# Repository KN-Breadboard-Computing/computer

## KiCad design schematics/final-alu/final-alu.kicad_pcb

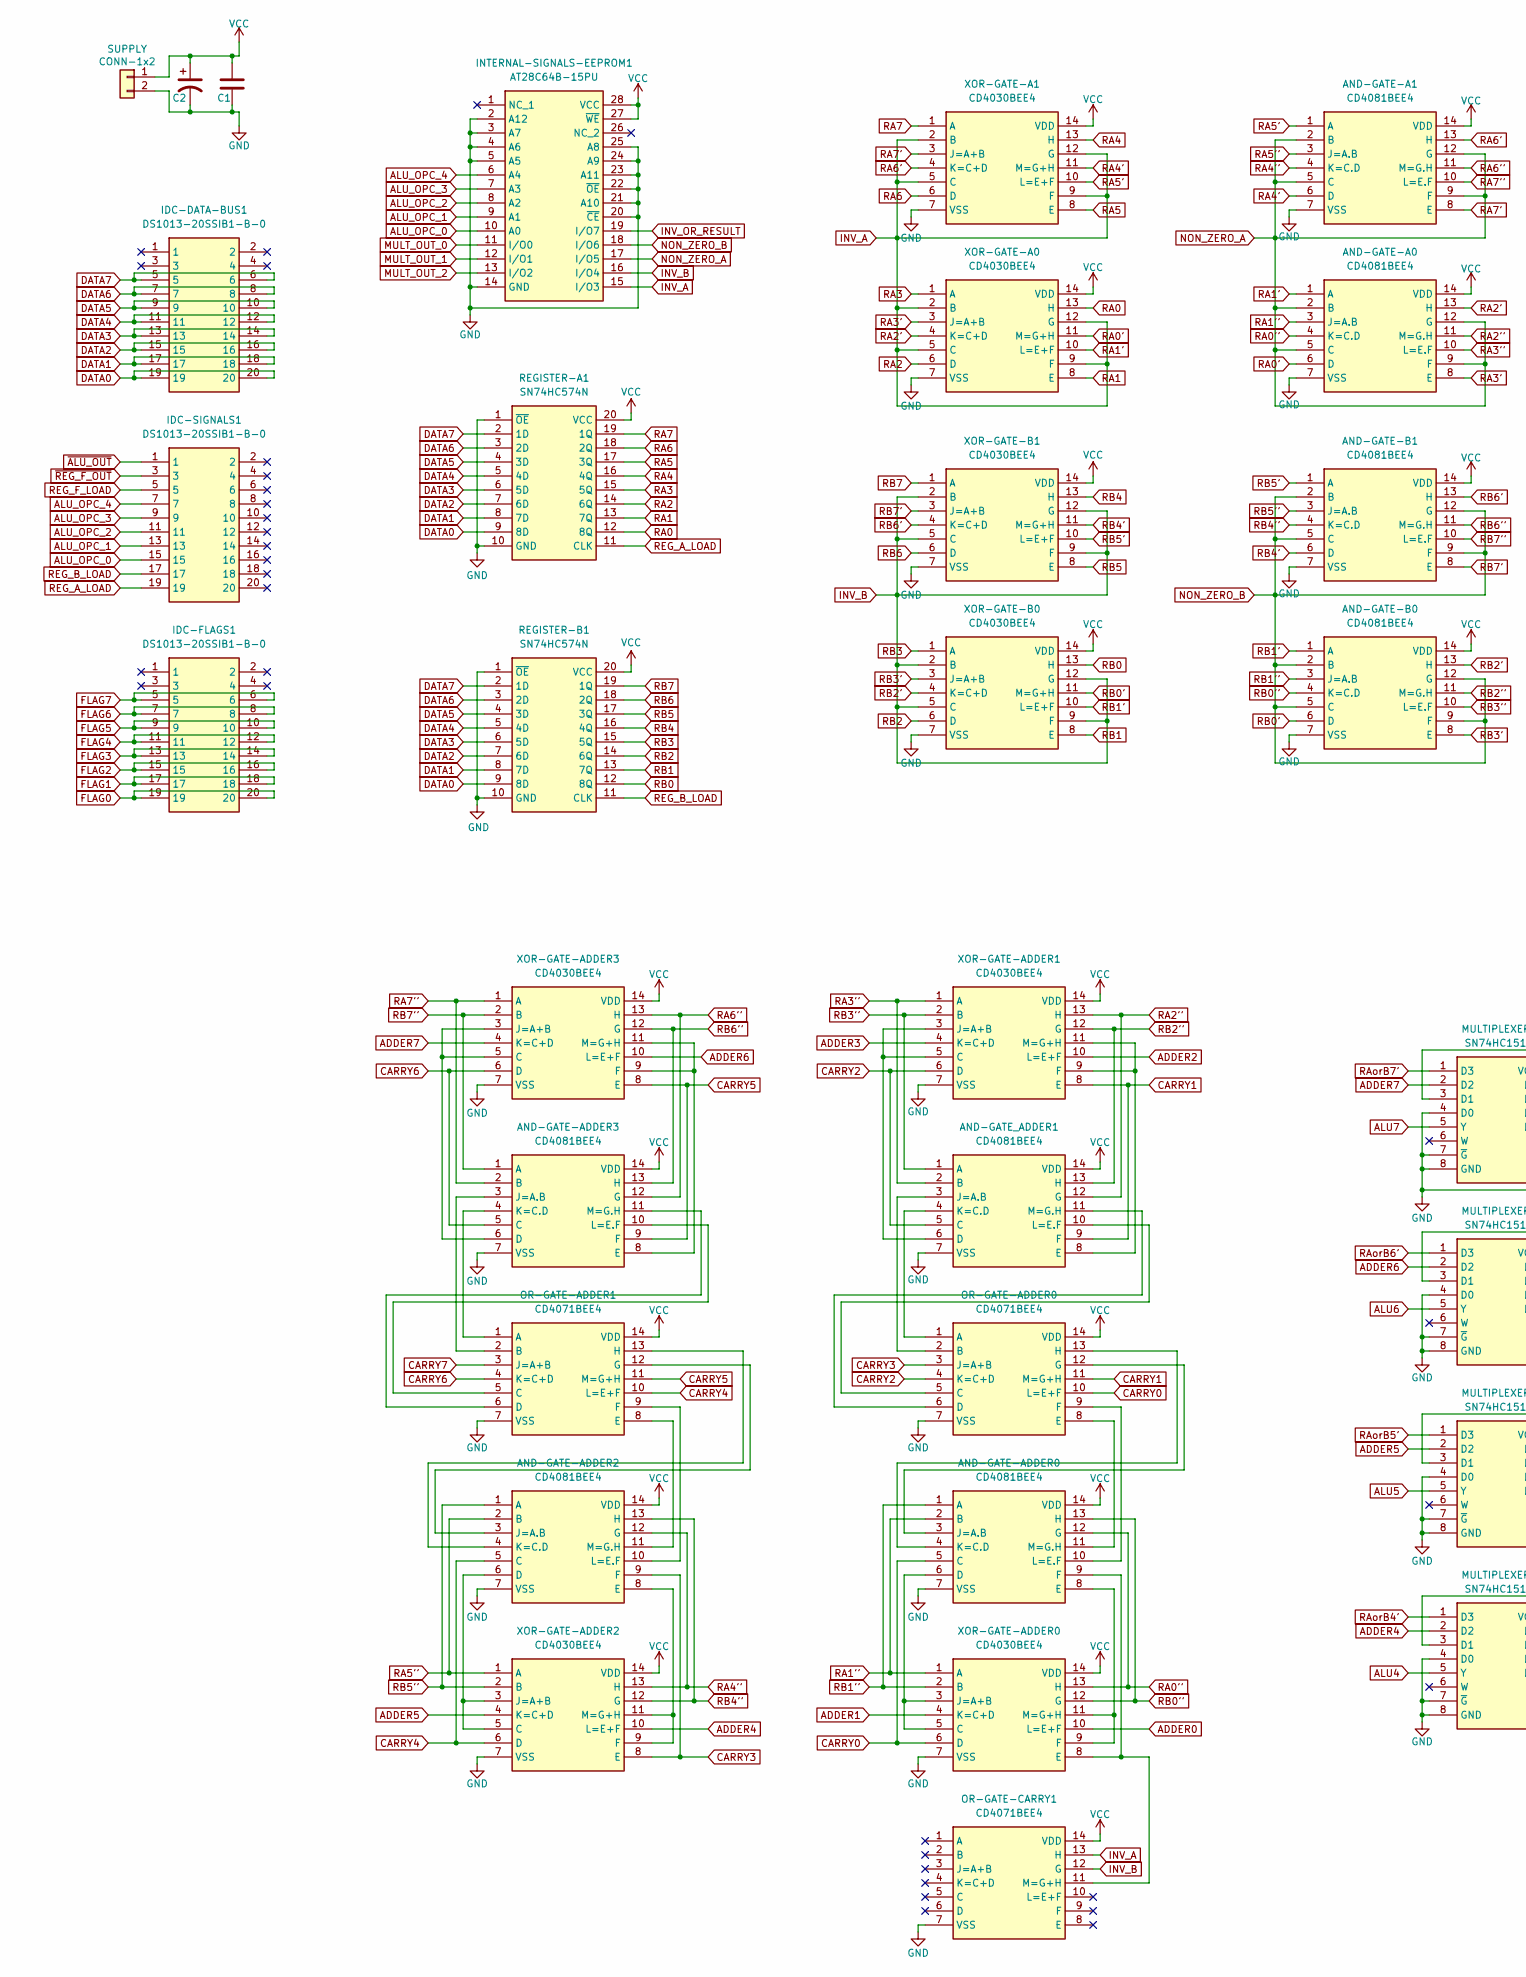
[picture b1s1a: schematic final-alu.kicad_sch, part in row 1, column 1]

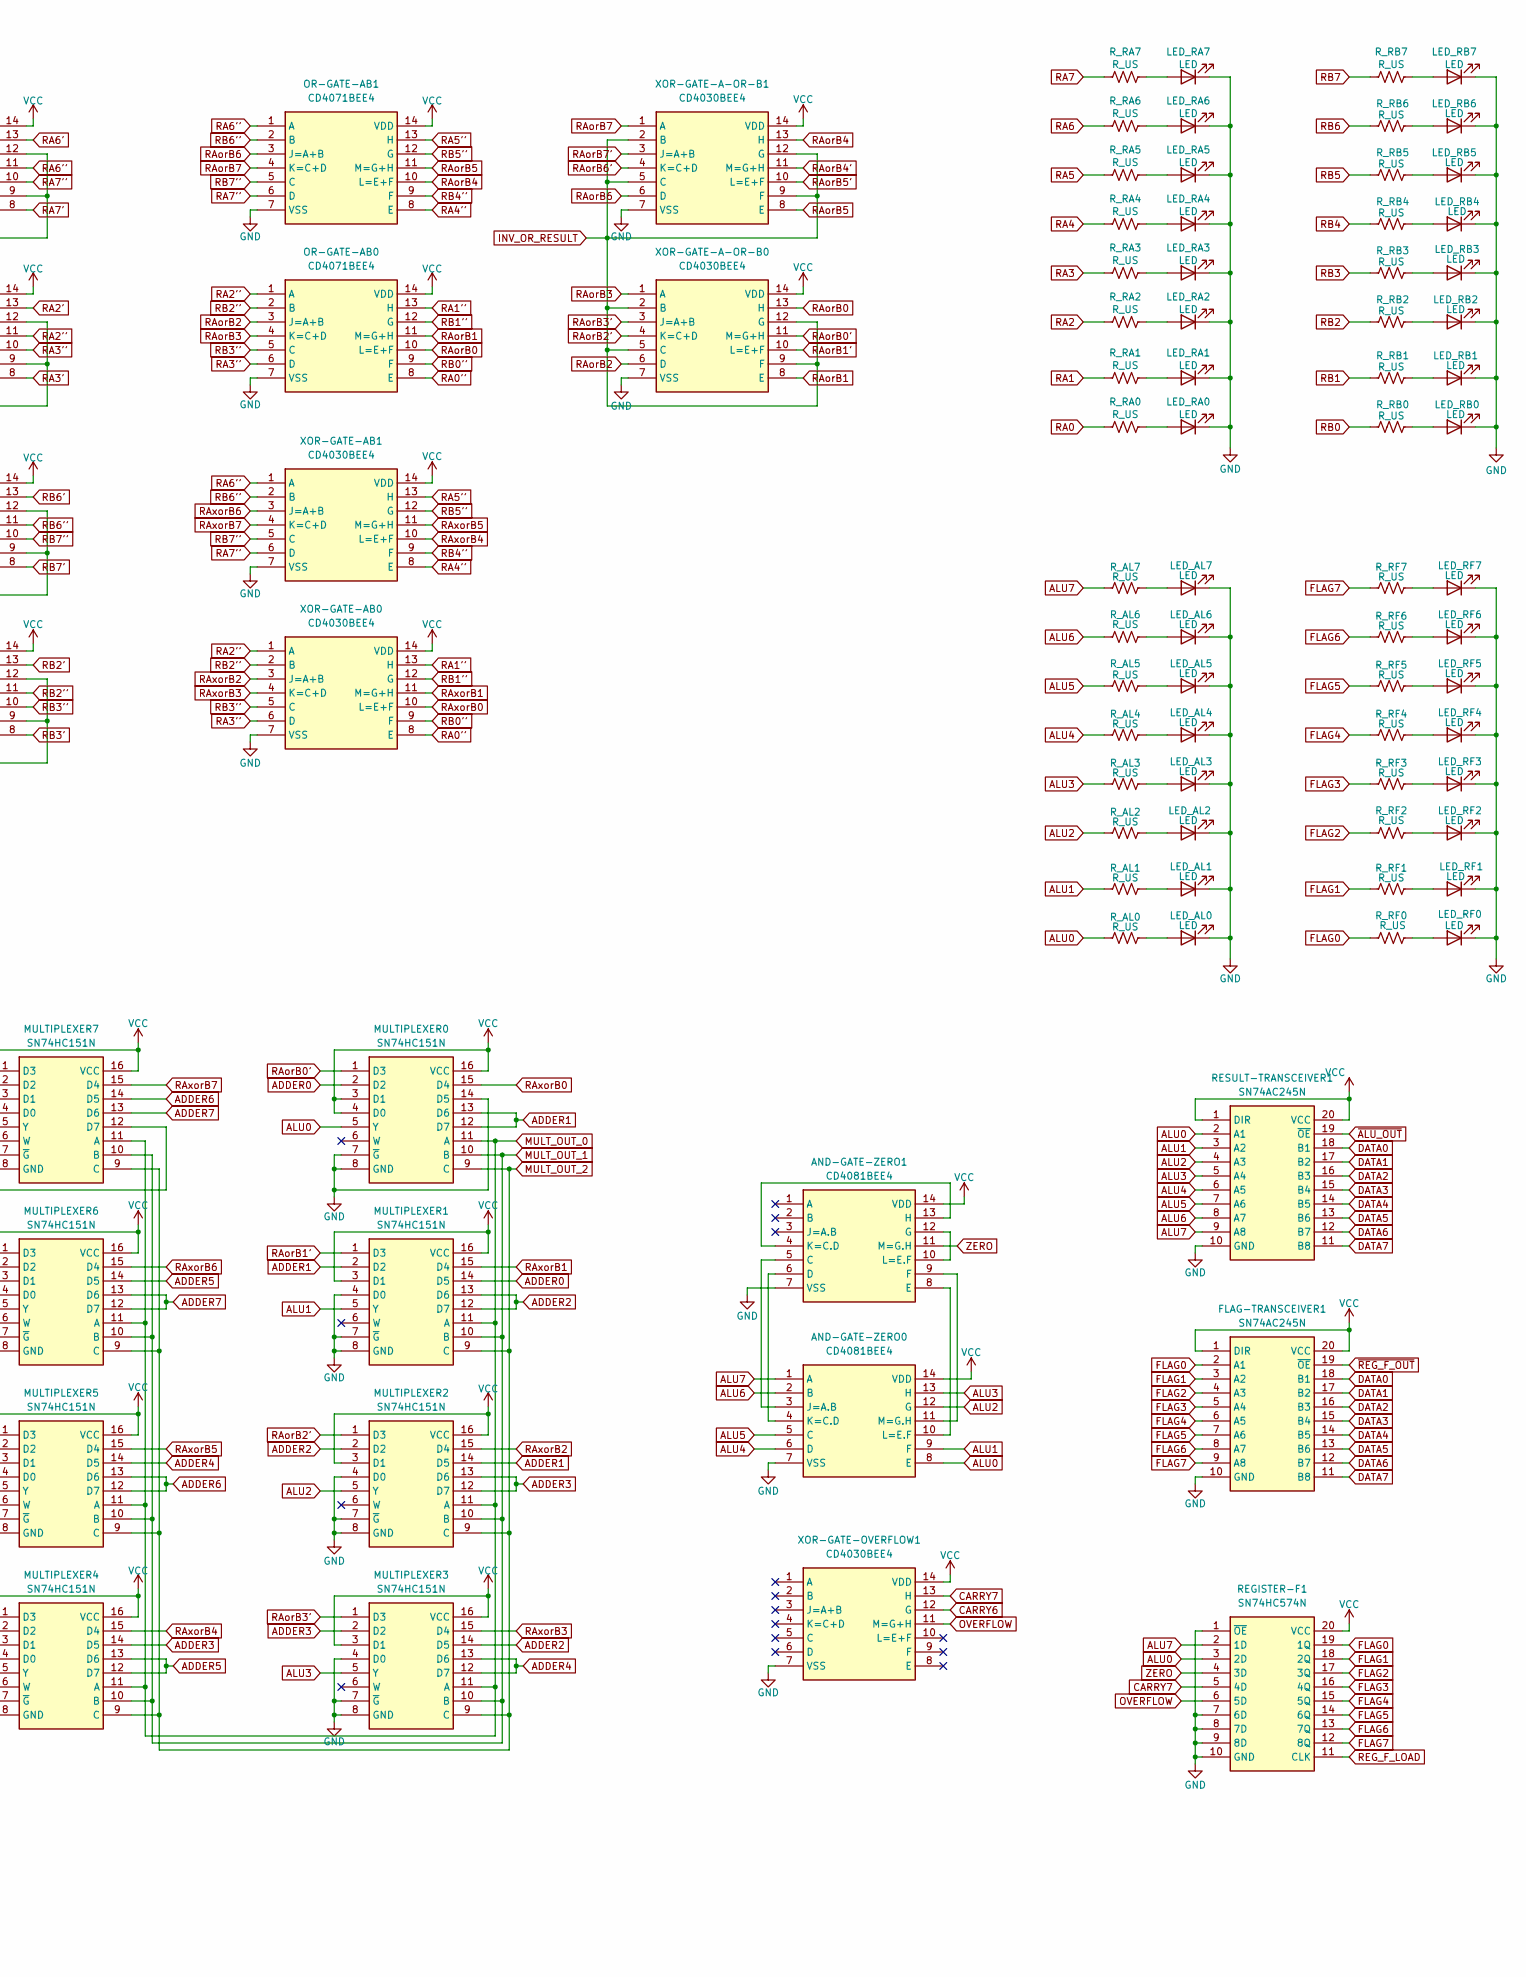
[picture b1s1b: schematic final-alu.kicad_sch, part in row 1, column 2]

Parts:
AND-GATE-A0, AND-GATE-A1: CD4081BEE4; DIP-14_W7.62mm; Mouser Part Number 595-CD4081BEE4
AND-GATE-ADDER0, AND-GATE-ADDER2, AND-GATE-ADDER3: CD4081BEE4; DIP-14_W7.62mm; Mouser Part Number 595-CD4081BEE4
AND-GATE-B0, AND-GATE-B1: CD4081BEE4; DIP-14_W7.62mm; Mouser Part Number 595-CD4081BEE4
AND-GATE-ZERO0, AND-GATE-ZERO1: CD4081BEE4; DIP-14_W7.62mm; Mouser Part Number 595-CD4081BEE4
AND-GATE_ADDER1: CD4081BEE4; DIP-14_W7.62mm; Mouser Part Number 595-CD4081BEE4
C1: C_Disc_D3.0mm_W1.6mm_P2.50mm
C2: CP_Radial_D5.0mm_P2.50mm
FLAG-TRANSCEIVER1: SN74AC245N; DIP-20_W7.62mm; Mouser Part Number 595-SN74AC245N
IDC-DATA-BUS1: DS1013-20SSIB1-B-0; PinSocket_2x10_P2.54mm_Vertical; Manufacturer_Part_Number DS1013-20SSIB1-B-0
IDC-FLAGS1: DS1013-20SSIB1-B-0; PinSocket_2x10_P2.54mm_Vertical; Manufacturer_Part_Number DS1013-20SSIB1-B-0
IDC-SIGNALS1: DS1013-20SSIB1-B-0; PinSocket_2x10_P2.54mm_Vertical; Manufacturer_Part_Number DS1013-20SSIB1-B-0
INTERNAL-SIGNALS-EEPROM1: AT28C64B-15PU; DIP-28_W15.24mm; Mouser Part Number 556-AT28C64B15PU
LED_AL0, LED_AL1, LED_AL2, LED_AL3, LED_AL4, LED_AL5, LED_AL6, LED_AL7: LED; LED_D5.0mm_FlatTop
LED_RA0, LED_RA1, LED_RA2, LED_RA3, LED_RA4, LED_RA5, LED_RA6, LED_RA7: LED; LED_D5.0mm_FlatTop
LED_RB0, LED_RB1, LED_RB2, LED_RB3, LED_RB4, LED_RB5, LED_RB6, LED_RB7: LED; LED_D5.0mm_FlatTop
LED_RF0, LED_RF1, LED_RF2, LED_RF3, LED_RF4, LED_RF5, LED_RF6, LED_RF7: LED; LED_D5.0mm_FlatTop
MULTIPLEXER0, MULTIPLEXER1, MULTIPLEXER2, MULTIPLEXER3, MULTIPLEXER4, MULTIPLEXER5, MULTIPLEXER6, MULTIPLEXER7: SN74HC151N; DIP-16_W7.62mm; Mouser Part Number 595-SN74HC151N
OR-GATE-AB0, OR-GATE-AB1: CD4071BEE4; DIP-14_W7.62mm; Mouser Part Number 595-CD4071BEE4
OR-GATE-ADDER0, OR-GATE-ADDER1: CD4071BEE4; DIP-14_W7.62mm; Mouser Part Number 595-CD4071BEE4
OR-GATE-CARRY1: CD4071BEE4; DIP-14_W7.62mm; Mouser Part Number 595-CD4071BEE4
REGISTER-A1: SN74HC574N; DIP-20_W7.62mm; Mouser Part Number 595-SN74HC574N
REGISTER-B1: SN74HC574N; DIP-20_W7.62mm; Mouser Part Number 595-SN74HC574N
REGISTER-F1: SN74HC574N; DIP-20_W7.62mm; Mouser Part Number 595-SN74HC574N
RESULT-TRANSCEIVER1: SN74AC245N; DIP-20_W7.62mm; Mouser Part Number 595-SN74AC245N
R_AL0, R_AL1, R_AL2, R_AL3, R_AL4, R_AL5, R_AL6, R_AL7: R_US; R_Axial_DIN0204_L3.6mm_D1.6mm_P7.62mm_Horizontal
R_RA0, R_RA1, R_RA2, R_RA3, R_RA4, R_RA5, R_RA6, R_RA7: R_US; R_Axial_DIN0204_L3.6mm_D1.6mm_P7.62mm_Horizontal
R_RB0, R_RB1, R_RB2, R_RB3, R_RB4, R_RB5, R_RB6, R_RB7: R_US; R_Axial_DIN0204_L3.6mm_D1.6mm_P7.62mm_Horizontal
R_RF0, R_RF1, R_RF2, R_RF3, R_RF4, R_RF5, R_RF6, R_RF7: R_US; R_Axial_DIN0204_L3.6mm_D1.6mm_P7.62mm_Horizontal
SUPPLY: CONN-1x2; PinHeader_1x02_P2.54mm_Vertical
XOR-GATE-A0, XOR-GATE-A1: CD4030BEE4; DIP-14_W7.62mm; Mouser Part Number 595-CD4030BEE4
XOR-GATE-A-OR-B0, XOR-GATE-A-OR-B1: CD4030BEE4; DIP-14_W7.62mm; Mouser Part Number 595-CD4030BEE4
XOR-GATE-AB0, XOR-GATE-AB1: CD4030BEE4; DIP-14_W7.62mm; Mouser Part Number 595-CD4030BEE4
XOR-GATE-ADDER0, XOR-GATE-ADDER1, XOR-GATE-ADDER2, XOR-GATE-ADDER3: CD4030BEE4; DIP-14_W7.62mm; Mouser Part Number 595-CD4030BEE4
XOR-GATE-B0, XOR-GATE-B1: CD4030BEE4; DIP-14_W7.62mm; Mouser Part Number 595-CD4030BEE4
XOR-GATE-OVERFLOW1: CD4030BEE4; DIP-14_W7.62mm; Mouser Part Number 595-CD4030BEE4

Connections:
ADDER0: MULTIPLEXER0.2 (D2), MULTIPLEXER1.14 (D5), XOR-GATE-ADDER0.10 (L=E+F)
ADDER1: MULTIPLEXER0.12 (D7), MULTIPLEXER0.13 (D6), MULTIPLEXER1.2 (D2), MULTIPLEXER2.14 (D5), XOR-GATE-ADDER0.4 (K=C+D)
ADDER2: MULTIPLEXER1.12 (D7), MULTIPLEXER1.13 (D6), MULTIPLEXER2.2 (D2), MULTIPLEXER3.14 (D5), XOR-GATE-ADDER1.10 (L=E+F)
ADDER3: MULTIPLEXER2.12 (D7), MULTIPLEXER2.13 (D6), MULTIPLEXER3.2 (D2), MULTIPLEXER4.14 (D5), XOR-GATE-ADDER1.4 (K=C+D)
ADDER4: MULTIPLEXER3.12 (D7), MULTIPLEXER3.13 (D6), MULTIPLEXER4.2 (D2), MULTIPLEXER5.14 (D5), XOR-GATE-ADDER2.10 (L=E+F)
ADDER5: MULTIPLEXER4.12 (D7), MULTIPLEXER4.13 (D6), MULTIPLEXER5.2 (D2), MULTIPLEXER6.14 (D5), XOR-GATE-ADDER2.4 (K=C+D)
ADDER6: MULTIPLEXER5.12 (D7), MULTIPLEXER5.13 (D6), MULTIPLEXER6.2 (D2), MULTIPLEXER7.14 (D5), XOR-GATE-ADDER3.10 (L=E+F)
ADDER7: MULTIPLEXER6.12 (D7), MULTIPLEXER6.13 (D6), MULTIPLEXER7.2 (D2), MULTIPLEXER7.13 (D6), XOR-GATE-ADDER3.4 (K=C+D)
ALU0: AND-GATE-ZERO0.8 (E), MULTIPLEXER0.5 (Y), REGISTER-F1.3 (2D), RESULT-TRANSCEIVER1.2 (A1), R_AL0.1
ALU1: AND-GATE-ZERO0.9 (F), MULTIPLEXER1.5 (Y), RESULT-TRANSCEIVER1.3 (A2), R_AL1.1
ALU2: AND-GATE-ZERO0.12 (G), MULTIPLEXER2.5 (Y), RESULT-TRANSCEIVER1.4 (A3), R_AL2.1
ALU3: AND-GATE-ZERO0.13 (H), MULTIPLEXER3.5 (Y), RESULT-TRANSCEIVER1.5 (A4), R_AL3.1
ALU4: AND-GATE-ZERO0.6 (D), MULTIPLEXER4.5 (Y), RESULT-TRANSCEIVER1.6 (A5), R_AL4.1
ALU5: AND-GATE-ZERO0.5 (C), MULTIPLEXER5.5 (Y), RESULT-TRANSCEIVER1.7 (A6), R_AL5.1
ALU6: AND-GATE-ZERO0.2 (B), MULTIPLEXER6.5 (Y), RESULT-TRANSCEIVER1.8 (A7), R_AL6.1
ALU7: AND-GATE-ZERO0.1 (A), MULTIPLEXER7.5 (Y), REGISTER-F1.2 (1D), RESULT-TRANSCEIVER1.9 (A8), R_AL7.2
ALU_OPC_0: IDC-SIGNALS1.15, INTERNAL-SIGNALS-EEPROM1.10 (A0)
ALU_OPC_1: IDC-SIGNALS1.13, INTERNAL-SIGNALS-EEPROM1.9 (A1)
ALU_OPC_2: IDC-SIGNALS1.11, INTERNAL-SIGNALS-EEPROM1.8 (A2)
ALU_OPC_3: IDC-SIGNALS1.9, INTERNAL-SIGNALS-EEPROM1.7 (A3)
ALU_OPC_4: IDC-SIGNALS1.7, INTERNAL-SIGNALS-EEPROM1.6 (A4)
CARRY0: AND-GATE-ADDER0.5 (C), OR-GATE-ADDER0.10 (L=E+F), XOR-GATE-ADDER0.6 (D)
CARRY1: AND-GATE_ADDER1.9 (F), OR-GATE-ADDER0.11 (M=G+H), XOR-GATE-ADDER1.8 (E)
CARRY2: AND-GATE_ADDER1.5 (C), OR-GATE-ADDER0.4 (K=C+D), XOR-GATE-ADDER1.6 (D)
CARRY3: AND-GATE-ADDER2.9 (F), OR-GATE-ADDER0.3 (J=A+B), XOR-GATE-ADDER2.8 (E)
CARRY4: AND-GATE-ADDER2.5 (C), OR-GATE-ADDER1.10 (L=E+F), XOR-GATE-ADDER2.6 (D)
CARRY5: AND-GATE-ADDER3.9 (F), OR-GATE-ADDER1.11 (M=G+H), XOR-GATE-ADDER3.8 (E)
CARRY6: AND-GATE-ADDER3.5 (C), OR-GATE-ADDER1.4 (K=C+D), XOR-GATE-ADDER3.6 (D), XOR-GATE-OVERFLOW1.12 (G)
CARRY7: OR-GATE-ADDER1.3 (J=A+B), REGISTER-F1.5 (4D), XOR-GATE-OVERFLOW1.13 (H)
DATA0: FLAG-TRANSCEIVER1.18 (B1), IDC-DATA-BUS1.19, IDC-DATA-BUS1.20, REGISTER-A1.9 (8D), REGISTER-B1.9 (8D), RESULT-TRANSCEIVER1.18 (B1)
DATA1: FLAG-TRANSCEIVER1.17 (B2), IDC-DATA-BUS1.17, IDC-DATA-BUS1.18, REGISTER-A1.8 (7D), REGISTER-B1.8 (7D), RESULT-TRANSCEIVER1.17 (B2)
DATA2: FLAG-TRANSCEIVER1.16 (B3), IDC-DATA-BUS1.15, IDC-DATA-BUS1.16, REGISTER-A1.7 (6D), REGISTER-B1.7 (6D), RESULT-TRANSCEIVER1.16 (B3)
DATA3: FLAG-TRANSCEIVER1.15 (B4), IDC-DATA-BUS1.13, IDC-DATA-BUS1.14, REGISTER-A1.6 (5D), REGISTER-B1.6 (5D), RESULT-TRANSCEIVER1.15 (B4)
DATA4: FLAG-TRANSCEIVER1.14 (B5), IDC-DATA-BUS1.11, IDC-DATA-BUS1.12, REGISTER-A1.5 (4D), REGISTER-B1.5 (4D), RESULT-TRANSCEIVER1.14 (B5)
DATA5: FLAG-TRANSCEIVER1.13 (B6), IDC-DATA-BUS1.9, IDC-DATA-BUS1.10, REGISTER-A1.4 (3D), REGISTER-B1.4 (3D), RESULT-TRANSCEIVER1.13 (B6)
DATA6: FLAG-TRANSCEIVER1.12 (B7), IDC-DATA-BUS1.7, IDC-DATA-BUS1.8, REGISTER-A1.3 (2D), REGISTER-B1.3 (2D), RESULT-TRANSCEIVER1.12 (B7)
DATA7: FLAG-TRANSCEIVER1.11 (B8), IDC-DATA-BUS1.5, IDC-DATA-BUS1.6, REGISTER-A1.2 (1D), REGISTER-B1.2 (1D), RESULT-TRANSCEIVER1.11 (B8)
GND: AND-GATE-A0.7 (VSS), AND-GATE-A1.7 (VSS), AND-GATE-ADDER0.7 (VSS), AND-GATE-ADDER2.7 (VSS), AND-GATE-ADDER3.7 (VSS), AND-GATE-B0.7 (VSS), AND-GATE-B1.7 (VSS), AND-GATE-ZERO0.7 (VSS), AND-GATE-ZERO1.7 (VSS), AND-GATE_ADDER1.7 (VSS), C1.2, C2.2, FLAG-TRANSCEIVER1.10 (GND), INTERNAL-SIGNALS-EEPROM1.2 (A12), INTERNAL-SIGNALS-EEPROM1.3 (A7), INTERNAL-SIGNALS-EEPROM1.4 (A6), INTERNAL-SIGNALS-EEPROM1.5 (A5), INTERNAL-SIGNALS-EEPROM1.14 (GND), INTERNAL-SIGNALS-EEPROM1.20 (~CE), INTERNAL-SIGNALS-EEPROM1.21 (A10), INTERNAL-SIGNALS-EEPROM1.22 (~OE), INTERNAL-SIGNALS-EEPROM1.23 (A11), INTERNAL-SIGNALS-EEPROM1.24 (A9), INTERNAL-SIGNALS-EEPROM1.25 (A8), LED_AL0.1 (K), LED_AL1.1 (K), LED_AL2.1 (K), LED_AL3.1 (K), LED_AL4.1 (K), LED_AL5.1 (K), LED_AL6.1 (K), LED_AL7.1 (K), LED_RA0.1 (K), LED_RA1.1 (K), LED_RA2.1 (K), LED_RA3.1 (K), LED_RA4.1 (K), LED_RA5.1 (K), LED_RA6.1 (K), LED_RA7.1 (K), LED_RB0.1 (K), LED_RB1.1 (K), LED_RB2.1 (K), LED_RB3.1 (K), LED_RB4.1 (K), LED_RB5.1 (K), LED_RB6.1 (K), LED_RB7.1 (K), LED_RF0.1 (K), LED_RF1.1 (K), LED_RF2.1 (K), LED_RF3.1 (K), LED_RF4.1 (K), LED_RF5.1 (K), LED_RF6.1 (K), LED_RF7.1 (K), MULTIPLEXER0.7 (~G), MULTIPLEXER0.8 (GND), MULTIPLEXER0.14 (D5), MULTIPLEXER1.4 (D0), MULTIPLEXER1.7 (~G), MULTIPLEXER1.8 (GND), MULTIPLEXER2.4 (D0), MULTIPLEXER2.7 (~G), MULTIPLEXER2.8 (GND), MULTIPLEXER3.4 (D0), MULTIPLEXER3.7 (~G), MULTIPLEXER3.8 (GND), MULTIPLEXER4.4 (D0), MULTIPLEXER4.7 (~G), MULTIPLEXER4.8 (GND), MULTIPLEXER5.4 (D0), MULTIPLEXER5.7 (~G), MULTIPLEXER5.8 (GND), MULTIPLEXER6.4 (D0), MULTIPLEXER6.7 (~G), MULTIPLEXER6.8 (GND), MULTIPLEXER7.4 (D0), MULTIPLEXER7.7 (~G), MULTIPLEXER7.8 (GND), MULTIPLEXER7.12 (D7), OR-GATE-AB0.7 (VSS), OR-GATE-AB1.7 (VSS), OR-GATE-ADDER0.7 (VSS), OR-GATE-ADDER1.7 (VSS), OR-GATE-CARRY1.7 (VSS), REGISTER-A1.1 (~OE), REGISTER-A1.10 (GND), REGISTER-B1.1 (~OE), REGISTER-B1.10 (GND), REGISTER-F1.1 (~OE), REGISTER-F1.7 (6D), REGISTER-F1.8 (7D), REGISTER-F1.9 (8D), REGISTER-F1.10 (GND), RESULT-TRANSCEIVER1.10 (GND), SUPPLY.2, XOR-GATE-A0.7 (VSS), XOR-GATE-A1.7 (VSS), XOR-GATE-A-OR-B0.7 (VSS), XOR-GATE-A-OR-B1.7 (VSS), XOR-GATE-AB0.7 (VSS), XOR-GATE-AB1.7 (VSS), XOR-GATE-ADDER0.7 (VSS), XOR-GATE-ADDER1.7 (VSS), XOR-GATE-ADDER2.7 (VSS), XOR-GATE-ADDER3.7 (VSS), XOR-GATE-B0.7 (VSS), XOR-GATE-B1.7 (VSS), XOR-GATE-OVERFLOW1.7 (VSS); also elsewhere on the board
INV_A: INTERNAL-SIGNALS-EEPROM1.15 (I/O3), OR-GATE-CARRY1.13 (H), XOR-GATE-A0.2 (B), XOR-GATE-A0.5 (C), XOR-GATE-A0.9 (F), XOR-GATE-A0.12 (G), XOR-GATE-A1.2 (B), XOR-GATE-A1.5 (C), XOR-GATE-A1.9 (F), XOR-GATE-A1.12 (G)
INV_B: INTERNAL-SIGNALS-EEPROM1.16 (I/O4), OR-GATE-CARRY1.12 (G), XOR-GATE-B0.2 (B), XOR-GATE-B0.5 (C), XOR-GATE-B0.9 (F), XOR-GATE-B0.12 (G), XOR-GATE-B1.2 (B), XOR-GATE-B1.5 (C), XOR-GATE-B1.9 (F), XOR-GATE-B1.12 (G)
INV_OR_RESULT: INTERNAL-SIGNALS-EEPROM1.19 (I/O7), XOR-GATE-A-OR-B0.2 (B), XOR-GATE-A-OR-B0.5 (C), XOR-GATE-A-OR-B0.9 (F), XOR-GATE-A-OR-B0.12 (G), XOR-GATE-A-OR-B1.2 (B), XOR-GATE-A-OR-B1.5 (C), XOR-GATE-A-OR-B1.9 (F), XOR-GATE-A-OR-B1.12 (G)
MULT_OUT_0: INTERNAL-SIGNALS-EEPROM1.11 (I/O0), MULTIPLEXER0.11 (A), MULTIPLEXER1.11 (A), MULTIPLEXER2.11 (A), MULTIPLEXER3.11 (A), MULTIPLEXER4.11 (A), MULTIPLEXER5.11 (A), MULTIPLEXER6.11 (A), MULTIPLEXER7.11 (A)
MULT_OUT_1: INTERNAL-SIGNALS-EEPROM1.12 (I/O1), MULTIPLEXER0.10 (B), MULTIPLEXER1.10 (B), MULTIPLEXER2.10 (B), MULTIPLEXER3.10 (B), MULTIPLEXER4.10 (B), MULTIPLEXER5.10 (B), MULTIPLEXER6.10 (B), MULTIPLEXER7.10 (B)
MULT_OUT_2: INTERNAL-SIGNALS-EEPROM1.13 (I/O2), MULTIPLEXER0.9 (C), MULTIPLEXER1.9 (C), MULTIPLEXER2.9 (C), MULTIPLEXER3.9 (C), MULTIPLEXER4.9 (C), MULTIPLEXER5.9 (C), MULTIPLEXER6.9 (C), MULTIPLEXER7.9 (C)
NON_ZERO_A: AND-GATE-A0.2 (B), AND-GATE-A0.5 (C), AND-GATE-A0.9 (F), AND-GATE-A0.12 (G), AND-GATE-A1.2 (B), AND-GATE-A1.5 (C), AND-GATE-A1.9 (F), AND-GATE-A1.12 (G), INTERNAL-SIGNALS-EEPROM1.17 (I/O5)
NON_ZERO_B: AND-GATE-B0.2 (B), AND-GATE-B0.5 (C), AND-GATE-B0.9 (F), AND-GATE-B0.12 (G), AND-GATE-B1.2 (B), AND-GATE-B1.5 (C), AND-GATE-B1.9 (F), AND-GATE-B1.12 (G), INTERNAL-SIGNALS-EEPROM1.18 (I/O6)
unnamed: AND-GATE-ADDER0.6 (D), XOR-GATE-ADDER0.3 (J=A+B), XOR-GATE-ADDER0.5 (C)
unnamed: AND-GATE-ADDER0.8 (E), XOR-GATE-ADDER0.9 (F), XOR-GATE-ADDER0.11 (M=G+H)
unnamed: AND-GATE-ADDER0.9 (F), OR-GATE-CARRY1.11 (M=G+H), XOR-GATE-ADDER0.8 (E)
unnamed: AND-GATE-ADDER0.3 (J=A.B), OR-GATE-ADDER0.12 (G)
unnamed: AND-GATE-ADDER0.4 (K=C.D), OR-GATE-ADDER0.13 (H)
unnamed: AND-GATE-ADDER0.10 (L=E.F), OR-GATE-ADDER0.9 (F)
unnamed: AND-GATE-ADDER0.11 (M=G.H), OR-GATE-ADDER0.8 (E)
unnamed: AND-GATE-ADDER2.6 (D), XOR-GATE-ADDER2.3 (J=A+B), XOR-GATE-ADDER2.5 (C)
unnamed: AND-GATE-ADDER2.8 (E), XOR-GATE-ADDER2.9 (F), XOR-GATE-ADDER2.11 (M=G+H)
unnamed: AND-GATE-ADDER2.3 (J=A.B), OR-GATE-ADDER1.12 (G)
unnamed: AND-GATE-ADDER2.4 (K=C.D), OR-GATE-ADDER1.13 (H)
unnamed: AND-GATE-ADDER2.10 (L=E.F), OR-GATE-ADDER1.9 (F)
unnamed: AND-GATE-ADDER2.11 (M=G.H), OR-GATE-ADDER1.8 (E)
unnamed: AND-GATE-ADDER3.6 (D), XOR-GATE-ADDER3.3 (J=A+B), XOR-GATE-ADDER3.5 (C)
unnamed: AND-GATE-ADDER3.8 (E), XOR-GATE-ADDER3.9 (F), XOR-GATE-ADDER3.11 (M=G+H)
unnamed: AND-GATE-ADDER3.3 (J=A.B), OR-GATE-ADDER1.2 (B)
unnamed: AND-GATE-ADDER3.4 (K=C.D), OR-GATE-ADDER1.1 (A)
unnamed: AND-GATE-ADDER3.10 (L=E.F), OR-GATE-ADDER1.5 (C)
unnamed: AND-GATE-ADDER3.11 (M=G.H), OR-GATE-ADDER1.6 (D)
unnamed: AND-GATE-ZERO0.3 (J=A.B), AND-GATE-ZERO1.5 (C)
unnamed: AND-GATE-ZERO0.4 (K=C.D), AND-GATE-ZERO1.6 (D)
unnamed: AND-GATE-ZERO0.10 (L=E.F), AND-GATE-ZERO1.8 (E)
unnamed: AND-GATE-ZERO0.11 (M=G.H), AND-GATE-ZERO1.9 (F)
unnamed: AND-GATE-ZERO1.10 (L=E.F), AND-GATE-ZERO1.12 (G)
unnamed: AND-GATE-ZERO1.4 (K=C.D), AND-GATE-ZERO1.13 (H)
unnamed: AND-GATE_ADDER1.6 (D), XOR-GATE-ADDER1.3 (J=A+B), XOR-GATE-ADDER1.5 (C)
unnamed: AND-GATE_ADDER1.8 (E), XOR-GATE-ADDER1.9 (F), XOR-GATE-ADDER1.11 (M=G+H)
unnamed: AND-GATE_ADDER1.3 (J=A.B), OR-GATE-ADDER0.2 (B)
unnamed: AND-GATE_ADDER1.4 (K=C.D), OR-GATE-ADDER0.1 (A)
unnamed: AND-GATE_ADDER1.10 (L=E.F), OR-GATE-ADDER0.5 (C)
unnamed: AND-GATE_ADDER1.11 (M=G.H), OR-GATE-ADDER0.6 (D)
unnamed: LED_AL0.2 (A), R_AL0.2
unnamed: LED_AL1.2 (A), R_AL1.2
unnamed: LED_AL2.2 (A), R_AL2.2
unnamed: LED_AL3.2 (A), R_AL3.2
unnamed: LED_AL4.2 (A), R_AL4.2
unnamed: LED_AL5.2 (A), R_AL5.2
unnamed: LED_AL6.2 (A), R_AL6.2
unnamed: LED_AL7.2 (A), R_AL7.1
unnamed: LED_RA0.2 (A), R_RA0.2
unnamed: LED_RA1.2 (A), R_RA1.2
unnamed: LED_RA2.2 (A), R_RA2.2
unnamed: LED_RA3.2 (A), R_RA3.2
unnamed: LED_RA4.2 (A), R_RA4.2
unnamed: LED_RA5.2 (A), R_RA5.2
unnamed: LED_RA6.2 (A), R_RA6.2
unnamed: LED_RA7.2 (A), R_RA7.2
unnamed: LED_RB0.2 (A), R_RB0.2
unnamed: LED_RB1.2 (A), R_RB1.2
unnamed: LED_RB2.2 (A), R_RB2.2
unnamed: LED_RB3.2 (A), R_RB3.2
unnamed: LED_RB4.2 (A), R_RB4.2
unnamed: LED_RB5.2 (A), R_RB5.2
unnamed: LED_RB6.2 (A), R_RB6.2
unnamed: LED_RB7.2 (A), R_RB7.2
unnamed: LED_RF0.2 (A), R_RF0.2
unnamed: LED_RF1.2 (A), R_RF1.2
unnamed: LED_RF2.2 (A), R_RF2.2
unnamed: LED_RF3.2 (A), R_RF3.2
unnamed: LED_RF4.2 (A), R_RF4.1
unnamed: LED_RF5.2 (A), R_RF5.2
unnamed: LED_RF6.2 (A), R_RF6.1
unnamed: LED_RF7.2 (A), R_RF7.2
OVERFLOW: REGISTER-F1.6 (5D), XOR-GATE-OVERFLOW1.11 (M=G+H)
RA0: REGISTER-A1.12 (8Q), R_RA0.1, XOR-GATE-A0.13 (H)
RA0': AND-GATE-A0.6 (D), XOR-GATE-A0.11 (M=G+H)
RA0'': AND-GATE-A0.4 (K=C.D), AND-GATE-ADDER0.12 (G), OR-GATE-AB0.8 (E), XOR-GATE-AB0.8 (E), XOR-GATE-ADDER0.13 (H)
RA1: REGISTER-A1.13 (7Q), R_RA1.1, XOR-GATE-A0.8 (E)
RA1': AND-GATE-A0.1 (A), XOR-GATE-A0.10 (L=E+F)
RA1'': AND-GATE-A0.3 (J=A.B), AND-GATE-ADDER0.2 (B), OR-GATE-AB0.13 (H), XOR-GATE-AB0.13 (H), XOR-GATE-ADDER0.1 (A)
RA2: REGISTER-A1.14 (6Q), R_RA2.1, XOR-GATE-A0.6 (D)
RA2': AND-GATE-A0.13 (H), XOR-GATE-A0.4 (K=C+D)
RA2'': AND-GATE-A0.11 (M=G.H), AND-GATE_ADDER1.12 (G), OR-GATE-AB0.1 (A), XOR-GATE-AB0.1 (A), XOR-GATE-ADDER1.13 (H)
RA3: REGISTER-A1.15 (5Q), R_RA3.1, XOR-GATE-A0.1 (A)
RA3': AND-GATE-A0.8 (E), XOR-GATE-A0.3 (J=A+B)
RA3'': AND-GATE-A0.10 (L=E.F), AND-GATE_ADDER1.2 (B), OR-GATE-AB0.6 (D), XOR-GATE-AB0.6 (D), XOR-GATE-ADDER1.1 (A)
RA4: REGISTER-A1.16 (4Q), R_RA4.1, XOR-GATE-A1.13 (H)
RA4': AND-GATE-A1.6 (D), XOR-GATE-A1.11 (M=G+H)
RA4'': AND-GATE-A1.4 (K=C.D), AND-GATE-ADDER2.12 (G), OR-GATE-AB1.8 (E), XOR-GATE-AB1.8 (E), XOR-GATE-ADDER2.13 (H)
RA5: REGISTER-A1.17 (3Q), R_RA5.1, XOR-GATE-A1.8 (E)
RA5': AND-GATE-A1.1 (A), XOR-GATE-A1.10 (L=E+F)
RA5'': AND-GATE-A1.3 (J=A.B), AND-GATE-ADDER2.2 (B), OR-GATE-AB1.13 (H), XOR-GATE-AB1.13 (H), XOR-GATE-ADDER2.1 (A)
RA6: REGISTER-A1.18 (2Q), R_RA6.1, XOR-GATE-A1.6 (D)
RA6': AND-GATE-A1.13 (H), XOR-GATE-A1.4 (K=C+D)
RA6'': AND-GATE-A1.11 (M=G.H), AND-GATE-ADDER3.12 (G), OR-GATE-AB1.1 (A), XOR-GATE-AB1.1 (A), XOR-GATE-ADDER3.13 (H)
RA7: REGISTER-A1.19 (1Q), R_RA7.1, XOR-GATE-A1.1 (A)
RA7': AND-GATE-A1.8 (E), XOR-GATE-A1.3 (J=A+B)
RA7'': AND-GATE-A1.10 (L=E.F), AND-GATE-ADDER3.2 (B), OR-GATE-AB1.6 (D), XOR-GATE-AB1.6 (D), XOR-GATE-ADDER3.1 (A)
RAorB0: OR-GATE-AB0.10 (L=E+F), XOR-GATE-A-OR-B0.13 (H)
RAorB0': MULTIPLEXER0.1 (D3), XOR-GATE-A-OR-B0.11 (M=G+H)
RAorB1: OR-GATE-AB0.11 (M=G+H), XOR-GATE-A-OR-B0.8 (E)
RAorB1': MULTIPLEXER1.1 (D3), XOR-GATE-A-OR-B0.10 (L=E+F)
RAorB2: OR-GATE-AB0.3 (J=A+B), XOR-GATE-A-OR-B0.6 (D)
RAorB2': MULTIPLEXER2.1 (D3), XOR-GATE-A-OR-B0.4 (K=C+D)
RAorB3: OR-GATE-AB0.4 (K=C+D), XOR-GATE-A-OR-B0.1 (A)
RAorB3': MULTIPLEXER3.1 (D3), XOR-GATE-A-OR-B0.3 (J=A+B)
RAorB4: OR-GATE-AB1.10 (L=E+F), XOR-GATE-A-OR-B1.13 (H)
RAorB4': MULTIPLEXER4.1 (D3), XOR-GATE-A-OR-B1.11 (M=G+H)
RAorB5: OR-GATE-AB1.11 (M=G+H), XOR-GATE-A-OR-B1.8 (E)
RAorB5': MULTIPLEXER5.1 (D3), XOR-GATE-A-OR-B1.10 (L=E+F)
RAorB6: OR-GATE-AB1.3 (J=A+B), XOR-GATE-A-OR-B1.6 (D)
RAorB6': MULTIPLEXER6.1 (D3), XOR-GATE-A-OR-B1.4 (K=C+D)
RAorB7: OR-GATE-AB1.4 (K=C+D), XOR-GATE-A-OR-B1.1 (A)
RAorB7': MULTIPLEXER7.1 (D3), XOR-GATE-A-OR-B1.3 (J=A+B)
RAxorB0: MULTIPLEXER0.15 (D4), XOR-GATE-AB0.10 (L=E+F)
RAxorB1: MULTIPLEXER1.15 (D4), XOR-GATE-AB0.11 (M=G+H)
RAxorB2: MULTIPLEXER2.15 (D4), XOR-GATE-AB0.3 (J=A+B)
RAxorB3: MULTIPLEXER3.15 (D4), XOR-GATE-AB0.4 (K=C+D)
RAxorB4: MULTIPLEXER4.15 (D4), XOR-GATE-AB1.10 (L=E+F)
RAxorB5: MULTIPLEXER5.15 (D4), XOR-GATE-AB1.11 (M=G+H)
RAxorB6: MULTIPLEXER6.15 (D4), XOR-GATE-AB1.3 (J=A+B)
RAxorB7: MULTIPLEXER7.15 (D4), XOR-GATE-AB1.4 (K=C+D)
RB0: REGISTER-B1.12 (8Q), R_RB0.1, XOR-GATE-B0.13 (H)
RB0': AND-GATE-B0.6 (D), XOR-GATE-B0.11 (M=G+H)
RB0'': AND-GATE-ADDER0.13 (H), AND-GATE-B0.4 (K=C.D), OR-GATE-AB0.9 (F), XOR-GATE-AB0.9 (F), XOR-GATE-ADDER0.12 (G)
RB1: REGISTER-B1.13 (7Q), R_RB1.1, XOR-GATE-B0.8 (E)
RB1': AND-GATE-B0.1 (A), XOR-GATE-B0.10 (L=E+F)
RB1'': AND-GATE-ADDER0.1 (A), AND-GATE-B0.3 (J=A.B), OR-GATE-AB0.12 (G), XOR-GATE-AB0.12 (G), XOR-GATE-ADDER0.2 (B)
RB2: REGISTER-B1.14 (6Q), R_RB2.1, XOR-GATE-B0.6 (D)
RB2': AND-GATE-B0.13 (H), XOR-GATE-B0.4 (K=C+D)
RB2'': AND-GATE-B0.11 (M=G.H), AND-GATE_ADDER1.13 (H), OR-GATE-AB0.2 (B), XOR-GATE-AB0.2 (B), XOR-GATE-ADDER1.12 (G)
RB3: REGISTER-B1.15 (5Q), R_RB3.1, XOR-GATE-B0.1 (A)
RB3': AND-GATE-B0.8 (E), XOR-GATE-B0.3 (J=A+B)
RB3'': AND-GATE-B0.10 (L=E.F), AND-GATE_ADDER1.1 (A), OR-GATE-AB0.5 (C), XOR-GATE-AB0.5 (C), XOR-GATE-ADDER1.2 (B)
RB4: REGISTER-B1.16 (4Q), R_RB4.1, XOR-GATE-B1.13 (H)
RB4': AND-GATE-B1.6 (D), XOR-GATE-B1.11 (M=G+H)
RB4'': AND-GATE-ADDER2.13 (H), AND-GATE-B1.4 (K=C.D), OR-GATE-AB1.9 (F), XOR-GATE-AB1.9 (F), XOR-GATE-ADDER2.12 (G)
RB5: REGISTER-B1.17 (3Q), R_RB5.1, XOR-GATE-B1.8 (E)
RB5': AND-GATE-B1.1 (A), XOR-GATE-B1.10 (L=E+F)
RB5'': AND-GATE-ADDER2.1 (A), AND-GATE-B1.3 (J=A.B), OR-GATE-AB1.12 (G), XOR-GATE-AB1.12 (G), XOR-GATE-ADDER2.2 (B)
RB6: REGISTER-B1.18 (2Q), R_RB6.1, XOR-GATE-B1.6 (D)
RB6': AND-GATE-B1.13 (H), XOR-GATE-B1.4 (K=C+D)
RB6'': AND-GATE-ADDER3.13 (H), AND-GATE-B1.11 (M=G.H), OR-GATE-AB1.2 (B), XOR-GATE-AB1.2 (B), XOR-GATE-ADDER3.12 (G)
RB7: REGISTER-B1.19 (1Q), R_RB7.1, XOR-GATE-B1.1 (A)
RB7': AND-GATE-B1.8 (E), XOR-GATE-B1.3 (J=A+B)
RB7'': AND-GATE-ADDER3.1 (A), AND-GATE-B1.10 (L=E.F), OR-GATE-AB1.5 (C), XOR-GATE-AB1.5 (C), XOR-GATE-ADDER3.2 (B)
REG_A_LOAD: IDC-SIGNALS1.19, REGISTER-A1.11 (CLK)
REG_B_LOAD: IDC-SIGNALS1.17, REGISTER-B1.11 (CLK)
REG_F_LOAD: IDC-SIGNALS1.5, REGISTER-F1.11 (CLK)
VCC: AND-GATE-A0.14 (VDD), AND-GATE-A1.14 (VDD), AND-GATE-ADDER0.14 (VDD), AND-GATE-ADDER2.14 (VDD), AND-GATE-ADDER3.14 (VDD), AND-GATE-B0.14 (VDD), AND-GATE-B1.14 (VDD), AND-GATE-ZERO0.14 (VDD), AND-GATE-ZERO1.14 (VDD), AND-GATE_ADDER1.14 (VDD), C1.1, C2.1, FLAG-TRANSCEIVER1.1 (DIR), FLAG-TRANSCEIVER1.20 (VCC), INTERNAL-SIGNALS-EEPROM1.27 (~WE), INTERNAL-SIGNALS-EEPROM1.28 (VCC), MULTIPLEXER0.3 (D1), MULTIPLEXER0.4 (D0), MULTIPLEXER0.16 (VCC), MULTIPLEXER1.3 (D1), MULTIPLEXER1.16 (VCC), MULTIPLEXER2.3 (D1), MULTIPLEXER2.16 (VCC), MULTIPLEXER3.3 (D1), MULTIPLEXER3.16 (VCC), MULTIPLEXER4.3 (D1), MULTIPLEXER4.16 (VCC), MULTIPLEXER5.3 (D1), MULTIPLEXER5.16 (VCC), MULTIPLEXER6.3 (D1), MULTIPLEXER6.16 (VCC), MULTIPLEXER7.3 (D1), MULTIPLEXER7.16 (VCC), OR-GATE-AB0.14 (VDD), OR-GATE-AB1.14 (VDD), OR-GATE-ADDER0.14 (VDD), OR-GATE-ADDER1.14 (VDD), OR-GATE-CARRY1.14 (VDD), REGISTER-A1.20 (VCC), REGISTER-B1.20 (VCC), REGISTER-F1.20 (VCC), RESULT-TRANSCEIVER1.1 (DIR), RESULT-TRANSCEIVER1.20 (VCC), SUPPLY.1, XOR-GATE-A0.14 (VDD), XOR-GATE-A1.14 (VDD), XOR-GATE-A-OR-B0.14 (VDD), XOR-GATE-A-OR-B1.14 (VDD), XOR-GATE-AB0.14 (VDD), XOR-GATE-AB1.14 (VDD), XOR-GATE-ADDER0.14 (VDD), XOR-GATE-ADDER1.14 (VDD), XOR-GATE-ADDER2.14 (VDD), XOR-GATE-ADDER3.14 (VDD), XOR-GATE-B0.14 (VDD), XOR-GATE-B1.14 (VDD), XOR-GATE-OVERFLOW1.14 (VDD); also elsewhere on the board
ZERO: AND-GATE-ZERO1.11 (M=G.H), REGISTER-F1.4 (3D)
~ALU_OUT: IDC-SIGNALS1.1, RESULT-TRANSCEIVER1.19 (~OE)
~REG_F_OUT: FLAG-TRANSCEIVER1.19 (~OE), IDC-SIGNALS1.3

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
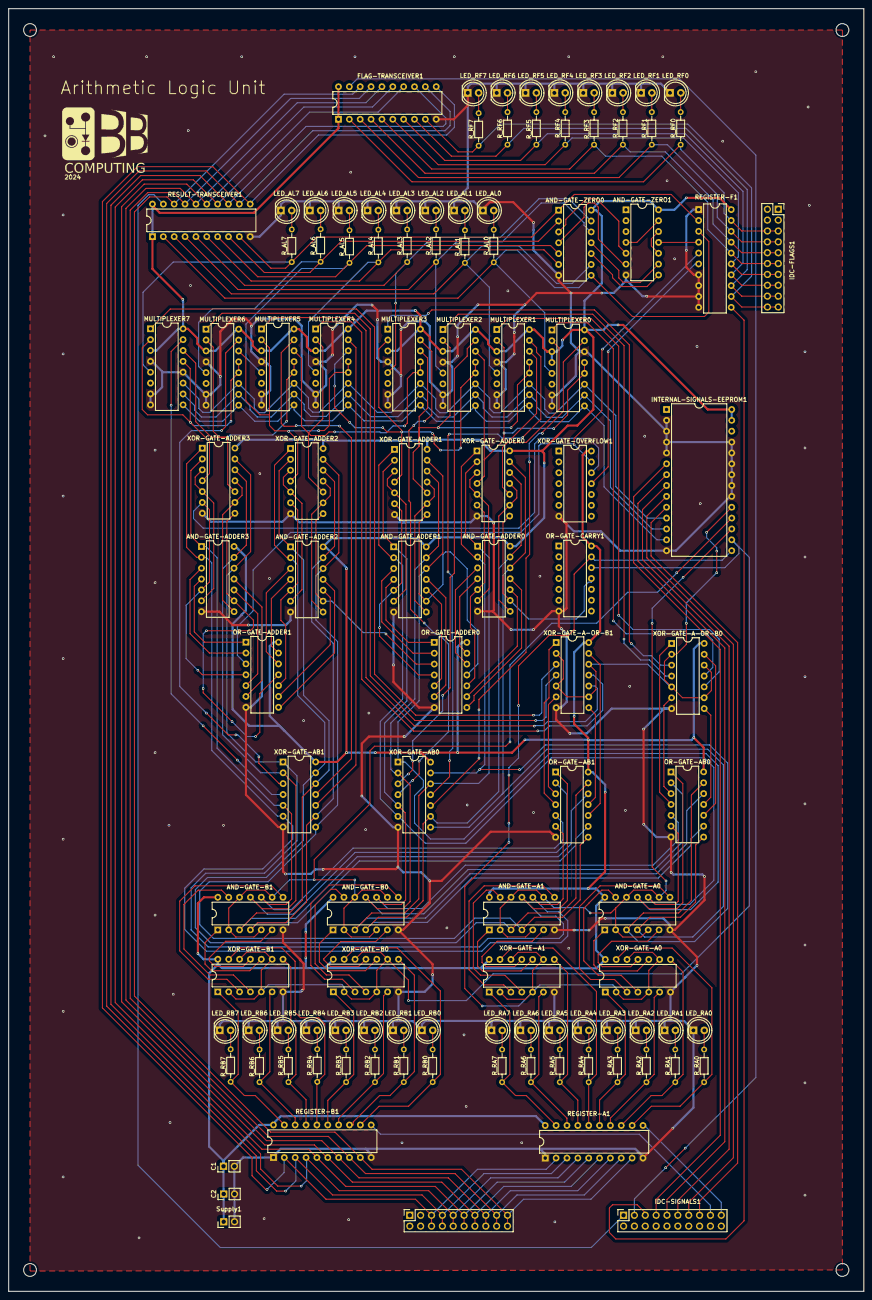
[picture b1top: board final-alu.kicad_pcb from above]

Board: 2 copper layers, 200.0 x 300.0 mm, 112 parts (0 on the bottom side), 197 nets.

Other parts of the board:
Supply1: Conn2; PinHeader_1x02_P2.54mm_Vertical

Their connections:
GND: Supply1.2; also elsewhere on the board
VCC: Supply1.1; also elsewhere on the board
